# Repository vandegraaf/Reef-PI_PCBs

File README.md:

# Reef-PI_PCBs
Contains schematics and PCB file for use with open source Reef-PI software

2 boards are presently uploaded:
HAT (interface to Raspberry 2 or 3) with following functions:
* Can drive up to 16 external relais modules
* Can drive up to 2 12V dosing pumps
* Can use up to 2 optical ATO (water) sensors
* Can drive multiple DS18B20 temperature sensors
* Can connect to external I2C boards (not yet tested)
It requires an external 12V power supply to operate the dosing pumps
This board has been tested (except I2C, but should be ok). No changes were made to the schematics, but some improvements to power and dosing connections have been made to the PCB
The HAT documentation contains all information of which connectors and related GPIO signals to use

New PWM module added
New Reef-PI_PWM v1.0 PCB files added (no documentation yet). These files have some minor improvements over the tested v0.3, mainly to avoid a potential collission with the DS18B20 connector on the Reef-PI_HAT. No changes have been made to the schematics between v0.3 and v1.0 of the PCB.
This Reef-PI_PWM module fits on top of the Reef-PI_HAT but can of course also be connected via wiring. It must be noted that the distance between the 2.5mm PWM output connectors is very small, only very small 2.5mm connectors will fit if all 16 channels are going to be used. The documentation provides a potential candidate.

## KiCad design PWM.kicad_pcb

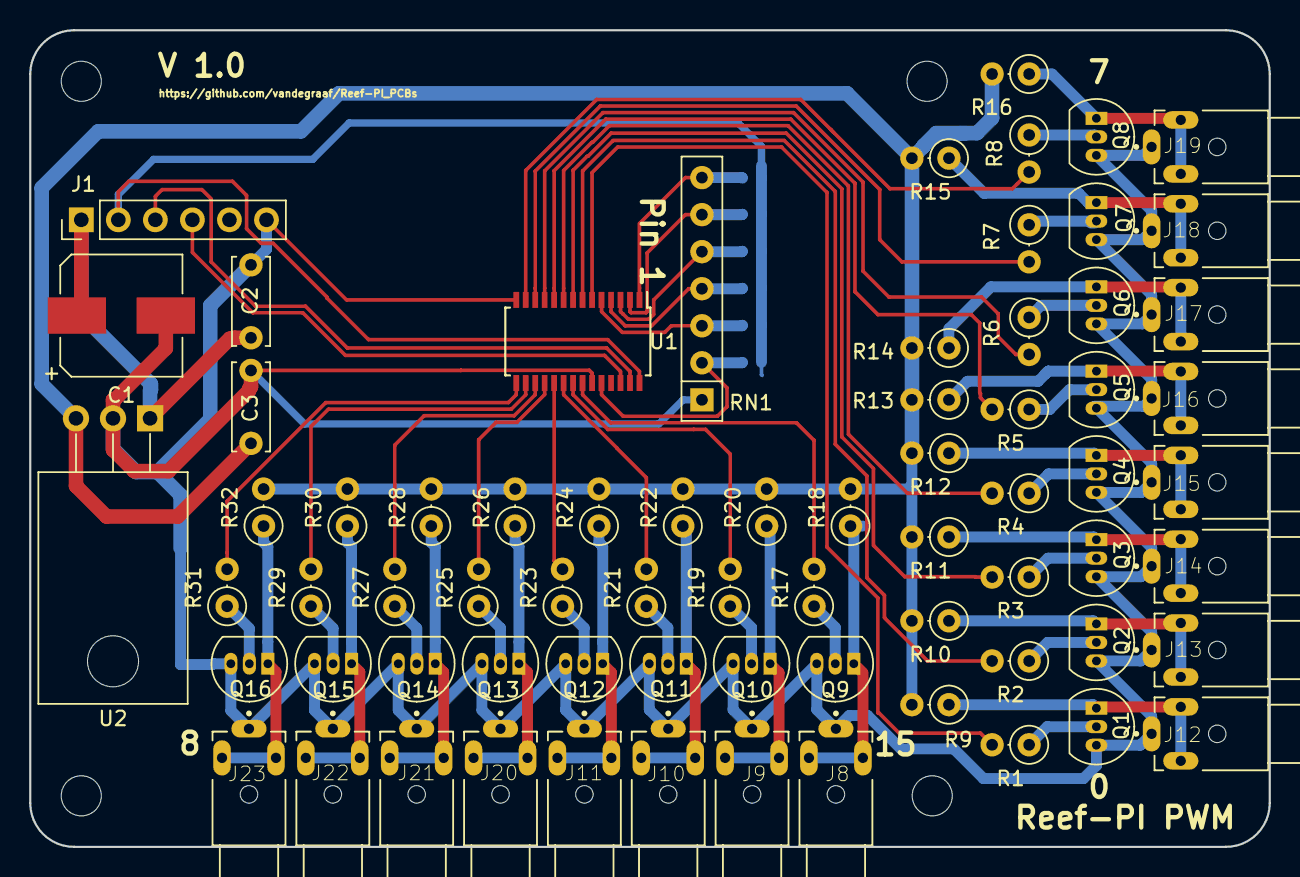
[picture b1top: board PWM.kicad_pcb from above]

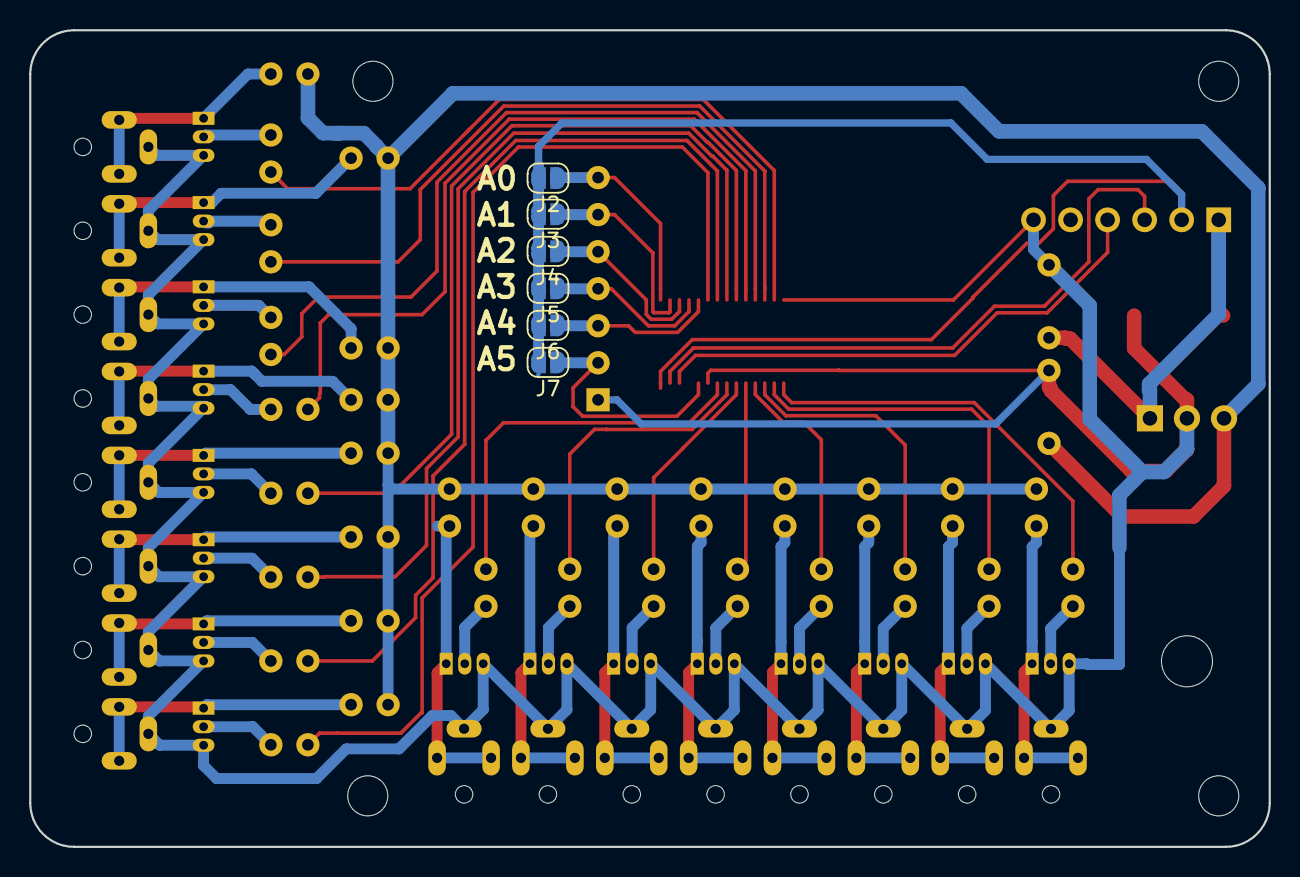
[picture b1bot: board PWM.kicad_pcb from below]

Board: 2 copper layers, 85.0 x 56.0 mm, 77 parts (6 on the bottom side), 60 nets.

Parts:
C1: 330uF; CP_Elec_8x10
C2, C3: 100nf; C_Disc_D6.0mm_W2.5mm_P5.00mm
J1: Conn_01x06_Male; Pin_Header_Straight_1x06_Pitch2.54mm
J2, J3, J4, J5, J6, J7: Jumper; SolderJumper-2_P1.3mm_Open_RoundedPad1.0x1.5mm
J8, J9, J10, J11, J12, J13, J14, J15, J16, J17, J18, J19, J20, J21, J22, J23: CUI_MJ1-2503A
Q1, Q2, Q3, Q4, Q5, Q6, Q7, Q8, Q9, Q10, Q11, Q12, Q13, Q14, Q15, Q16: BC184B; TO-92_Inline_Narrow_Oval
R1, R2, R3, R4, R5, R6, R7, R8, R17, R19, R21, R23, R25, R27, R29, R31: 10K; R_Axial_DIN0207_L6.3mm_D2.5mm_P2.54mm_Vertical
R9, R10, R11, R12, R13, R14, R15, R16, R18, R20, R22, R24, R26, R28, R30, R32: 1K; R_Axial_DIN0207_L6.3mm_D2.5mm_P2.54mm_Vertical
RN1: R_Network06; R_Array_SIP7
U1: PCA9685PW; TSSOP-28_4.4x9.7mm_Pitch0.65mm
U2: uA7810; TO-220-3_Horizontal

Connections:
GND: C1.2, C2.2, C3.2, J1.6, J8.1, J9.1, J10.1, J11.1, J12.1, J13.1, J14.1, J15.1, J16.1, J17.1, J18.1, J19.1, J20.1, J21.1, J22.1, J23.1, Q1.3, Q2.3, Q3.3, Q4.3, Q5.3, Q6.3, Q7.3, Q8.3, Q9.3, Q10.3, Q11.3, Q12.3, Q13.3, Q14.3, Q15.3, Q16.3, RN1.1, U1.14, U1.23, U2.2
unnamed: C1.1, C2.1, J1.1, U2.1
unnamed: C3.1, R9.2, R10.2, R11.2, R12.2, R13.2, R14.2, R15.2, R16.2, R18.2, R20.2, R22.2, R24.2, R26.2, R28.2, R30.2, R32.2, U2.3
unnamed: J1.2, J2.2, J3.2, J4.2, J5.2, J6.2, J7.2, U1.28
unnamed: J1.3, U1.27
unnamed: J1.4, U1.26
unnamed: J2.1, RN1.7, U1.1
unnamed: J3.1, RN1.6, U1.2
unnamed: J4.1, RN1.5, U1.3
unnamed: J5.1, RN1.4, U1.4
unnamed: J6.1, RN1.3, U1.5
unnamed: J7.1, RN1.2, U1.24
unnamed: J8.2, J8.3, Q9.1, R18.1
unnamed: J9.2, J9.3, Q10.1, R20.1
unnamed: J10.2, J10.3, Q11.1, R22.1
unnamed: J11.2, J11.3, Q12.1, R24.1
unnamed: J12.2, J12.3, Q1.1, R9.1
unnamed: J13.2, J13.3, Q2.1, R10.1
unnamed: J14.2, J14.3, Q3.1, R11.1
unnamed: J15.2, J15.3, Q4.1, R12.1
unnamed: J16.2, J16.3, Q5.1, R13.1
unnamed: J17.2, J17.3, Q6.1, R14.1
unnamed: J18.2, J18.3, Q7.1, R15.1
unnamed: J19.2, J19.3, Q8.1, R16.1
unnamed: J20.2, J20.3, Q13.1, R26.1
unnamed: J21.2, J21.3, Q14.1, R28.1
unnamed: J22.2, J22.3, Q15.1, R30.1
unnamed: J23.2, J23.3, Q16.1, R32.1
unnamed: Q1.2, R1.1
unnamed: Q2.2, R2.1
unnamed: Q3.2, R3.1
unnamed: Q4.2, R4.1
unnamed: Q5.2, R5.1
unnamed: Q6.2, R6.1
unnamed: Q7.2, R7.1
unnamed: Q8.2, R8.1
unnamed: Q9.2, R17.1
unnamed: Q10.2, R19.1
unnamed: Q11.2, R21.1
unnamed: Q12.2, R23.1
unnamed: Q13.2, R25.1
unnamed: Q14.2, R27.1
unnamed: Q15.2, R29.1
unnamed: Q16.2, R31.1
unnamed: R1.2, U1.6
unnamed: R2.2, U1.7
unnamed: R3.2, U1.8
unnamed: R4.2, U1.9
unnamed: R5.2, U1.10
unnamed: R6.2, U1.11
unnamed: R7.2, U1.12
unnamed: R8.2, U1.13
unnamed: R17.2, U1.22
unnamed: R19.2, U1.21
unnamed: R21.2, U1.20
unnamed: R23.2, U1.19
unnamed: R25.2, U1.18
unnamed: R27.2, U1.17
unnamed: R29.2, U1.16
unnamed: R31.2, U1.15

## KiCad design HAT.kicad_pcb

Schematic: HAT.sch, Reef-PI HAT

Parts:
C1, C6: 100nF; C_Disc_D6.0mm_W2.5mm_P5.00mm; MPN MMK5 104K50J01L4 BULK
C4: 100nF; C_Disc_D6.0mm_W2.5mm_P5.00mm; MPN MMK5104J50J01TR18L16.5TR18
C5: 10uF; CP_Radial_D6.3mm_P2.50mm; MPN 106RSS050M
J1: Conn_01x02; Pin_Header_Straight_1x02_Pitch2.54mm; MPN 651-1715022
J2: Conn_02x20_Odd_Even; Pin_Header_Straight_2x20_Pitch2.54mm; MPN 2-826925-0
J3, J4: Conn_01x02; Pin_Header_Straight_1x02_Pitch2.54mm
J5: Conn_01x03; CUI_SJ1-3533NG; MPN SJ1-3533NG
J6, J7: Conn_01x04; Pin_Header_Straight_1x04_Pitch2.54mm
J8: Conn_01x06; Pin_Header_Straight_1x06_Pitch2.54mm; MPN B6B-XH-A
J9: Conn_02x10_Odd_Even; Socket_Strip_Angled_2x10_Pitch2.54mm; MPN 2.54mm Pitch 2x10 Pin 20 Pin Female Dou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
R1, R3, R5: 4K7; R_Axial_DIN0207_L6.3mm_D2.5mm_P7.62mm_Horizontal; MPN CFR-25JT-52-4K7
R2, R4: 360; R_Axial_DIN0207_L6.3mm_D2.5mm_P7.62mm_Horizontal; MPN MFR-25FTE52-360R
U1: L293D; DIP-16_W7.62mm; MPN L293DNE
U2, U3: ULN2803A; DIP-18_W7.62mm; MPN ULN2803A

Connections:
GND: C1.2, C4.2, C5.2, C6.2, J1.1, J2.39, J5.1, J6.1, J6.2, J7.1, J7.2, J8.6, J9.19, J9.20, U1.4 (GND), U1.5 (GND), U1.12 (GND), U1.13 (GND), U2.9, U3.9
unnamed: C1.1, J2.11, J6.4, R1.2
unnamed: C4.1, J2.35, J7.4, R3.2
unnamed: C5.1, C6.1, J2.2, J2.4, J8.2, J9.1, J9.2, R1.1, R2.1, R3.1, R4.1, U1.16 (VCC1), U2.10, U3.10
unnamed: J1.2, J8.1, U1.8 (VCC2)
unnamed: J2.3, J8.3
unnamed: J2.5, J8.4
unnamed: J2.7, J5.2, R5.2
unnamed: J2.8, U1.7 (2A)
unnamed: J2.10, U1.10 (3A)
unnamed: J2.12, U1.1 (EN1,2), U1.9 (EN3,4)
unnamed: J2.13, U3.8
unnamed: J2.15, U3.3
unnamed: J2.16, U3.4
unnamed: J2.17, J5.3, R5.1
unnamed: J2.18, U3.5
unnamed: J2.19, U2.6
unnamed: J2.21, U2.5
unnamed: J2.22, U3.6
unnamed: J2.23, U2.7
unnamed: J2.24, U2.4
unnamed: J2.26, U2.3
unnamed: J2.29, U2.1
unnamed: J2.31, U2.2
unnamed: J2.32, U2.8
unnamed: J2.33, U1.2 (1A)
unnamed: J2.36, U1.15 (4A)
unnamed: J2.37, U3.7
unnamed: J2.38, U3.1
unnamed: J2.40, U3.2
unnamed: J3.1, U1.3 (1Y)
unnamed: J3.2, U1.6 (2Y)
unnamed: J4.1, U1.11 (3A)
unnamed: J4.2, U1.14 (4Y)
unnamed: J6.3, R2.2
unnamed: J7.3, R4.2
unnamed: J9.3, U2.11
unnamed: J9.4, U3.11
unnamed: J9.5, U2.12
unnamed: J9.6, U3.12
unnamed: J9.7, U2.13
unnamed: J9.8, U3.13
unnamed: J9.9, U2.14
unnamed: J9.10, U3.14
unnamed: J9.11, U2.15
unnamed: J9.12, U3.15
unnamed: J9.13, U2.16
unnamed: J9.14, U3.16
unnamed: J9.15, U2.17
unnamed: J9.16, U3.17
unnamed: J9.17, U2.18
unnamed: J9.18, U3.18

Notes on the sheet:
I2C
Dosing #1
Dosing #2
DS18B20 interface
ATO #1
ATO #2

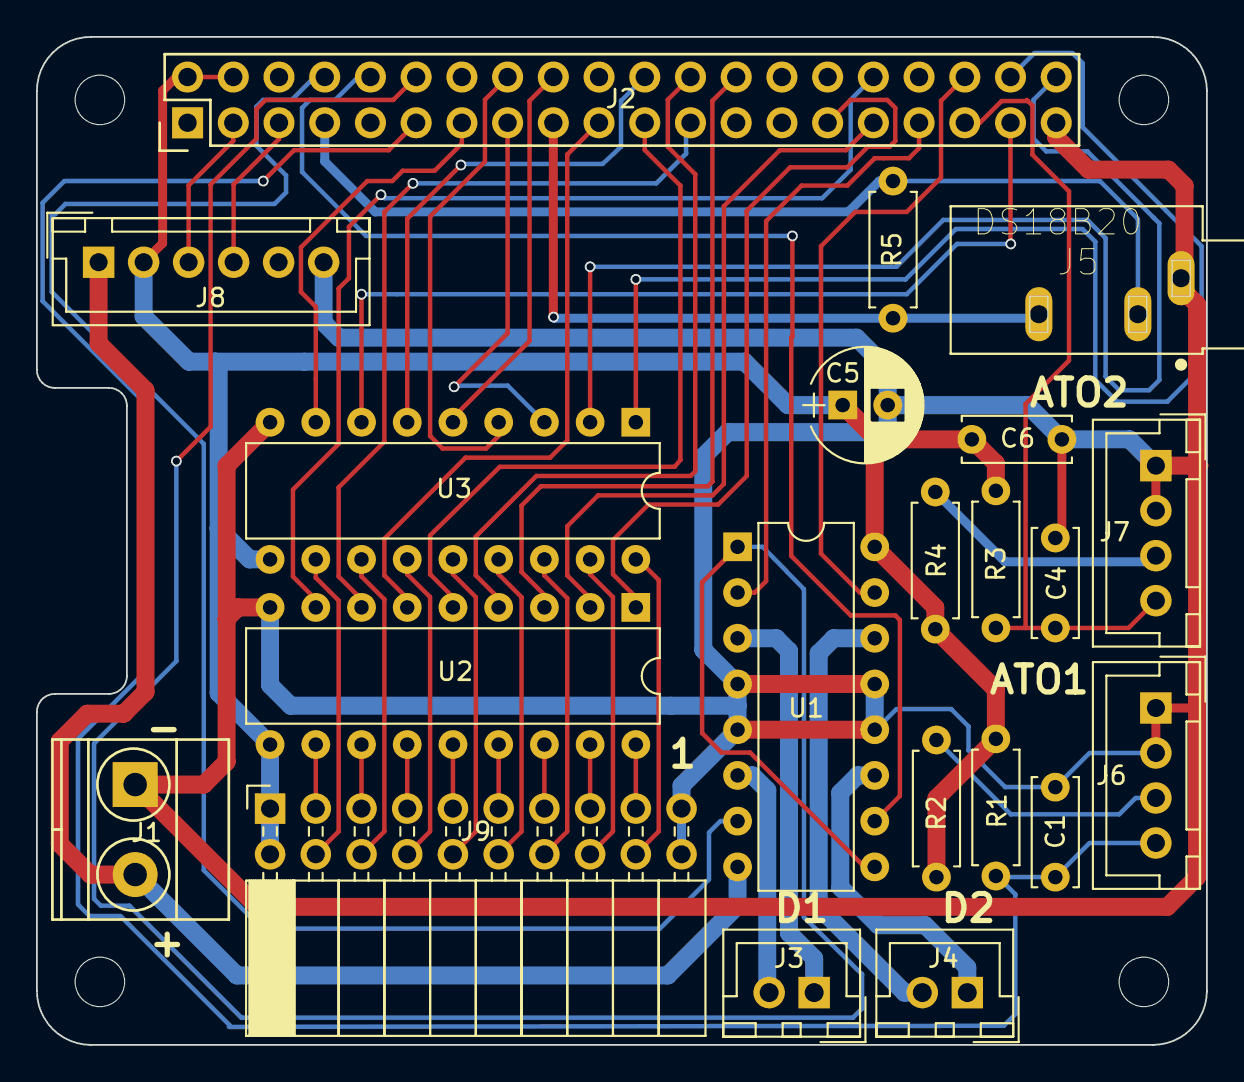
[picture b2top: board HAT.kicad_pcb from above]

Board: 2 copper layers, 65.0 x 56.0 mm, 21 parts (0 on the bottom side), 52 nets.

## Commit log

2018-08-06 PWM Kicad files v0.2 added
    These schematics and PCB lay-out have not been tested yet!
    Change to v0.1 are a misalignment of the output signals and removal of all via's
2018-08-06 PWM Kicad files v0.2 added
    DO NOTE: these schematics and PCB's have not been tested so far
    Changes to v0.1 are a misalignment of the output channels and removal of all via's
2018-08-06 BOM and housing parameters updated
2018-08-06 Updated Silk file
    Rotated transistors
2018-08-13 Reef_PI HAT files added
    This schematic for the HAT has been build and was fully functional. Nevertheless minor modifications have been made to the PCB (better grounding, larger connections to the dosing pumps), this should 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
    I've checked the boards at JLCPCB and they were completely accepted
    The HAT offers following functions:
    16 outputs to drive external relays
    2 Dosing outputs
    2 ATO inputs
2018-11-02 Update on Reef-PI_PWM module status
2018-11-07 Add files via upload
    Reviewed and updated BOM (HAT.csv file).
    Updated HAT documentation due to a failure in the DS18B20 temperature wiring description (thanks to Speedstar for this). At the same time other parts of the documentation have been updated and/or add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
    No changes are made to the Reef-PI HAT design (schematics/PCB)
2018-11-29 HAT building guideline added
2018-12-08 Reef-PI_PWM_v1.0 PCB files added
2018-12-22 Note: not complete and not updated to latest v0.3 layout
    This document needs to be updated to the latest v0.3 layout but these changes related to v0.2 layout are minimal
